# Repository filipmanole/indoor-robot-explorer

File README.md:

<!-- PROJECT SHIELDS -->
<!--
*** I'm using markdown "reference style" links for readability.
*** Reference links are enclosed in brackets [ ] instead of parentheses ( ).
*** See the bottom of this document for the declaration of the reference variables
*** for contributors-url, forks-url, etc. This is an optional, concise syntax you may use.
*** https://www.markdownguide.org/basic-syntax/#reference-style-links
-->

[![Contributors][contributors-shield]][contributors-url]
[![Forks][forks-shield]][forks-url]
[![Stargazers][stars-shield]][stars-url]
[![Issues][issues-shield]][issues-url]
[![LinkedIn][linkedin-shield]][linkedin-url]

<!-- PROJECT LOGO -->
<br />
<p align="center">

  <h1 align="center">Indoor Robot Explorer</h1>

  <p align="center">
    <a href="https://github.com/filipmanole/indoor-robot-explorer/issues">Report Bug</a>
    ·
    <a href="https://github.com/filipmanole/indoor-robot-explorer/issues">Request Feature</a>
  </p>
</p>

<!-- TABLE OF CONTENTS -->

## Table of Contents

- [About the Project](#about-the-project)
- [Software Tools](#software-tools)
- [Hardware](#hardware)
- [Getting Started](#getting-started)
  - [Prerequisites](#prerequisites)
  - [Usage](#usage)
- [Roadmap](#roadmap)
- [Contributing](#contributing)
- [License](#license)

<!-- ABOUT THE PROJECT -->

## About The Project

In recent years there has been an increase in interest in robots. There are billions of dollar spent on professional and personal use robots: autonomous vehicles, maintenance robots, cleaning robots. This repository offers a well structured, modular and low cost robot.

## Software Tools

Board layout was designed using [EAGLE 9.2.2](https://www.autodesk.com/products/eagle/overview?plc=F360&term=1-YEAR&support=ADVANCED&quantity=1)

Firmware was developed using:
- [MPLAB X 5.30](https://www.microchip.com/mplab/mplab-x-ide)
- dsPIC33E-GM-GP-MC-GU-MU_DFP 1.0.23
- [XC16](https://www.microchip.com/mplab/compilers) v1.50

Raspberry Pi specifications:
- [Raspbian GNU/Linux 9 (stretch)](https://www.raspberrypi.org/downloads/raspberry-pi-os/)
- [GCC](https://gcc.gnu.org/) version 6.3.0
- Python 2.7

## Hardware

### Main Components Used
- LiPo Battery 7V4 2200mA
- [dsPIC33EP128GM304](https://www.microchip.com/wwwproducts/en/dsPIC33EP128GM304) microcontroller
- 2x [MC33926](https://www.nxp.com/docs/en/data-sheet/MC33926.pdf) Motor Drivers
- 2x [Pololu ](https://www.pololu.com/product/2283) DC Motors
- 3x [VL53L0X]() Time of Flight Sensors
- [Raspberry Pi Zero W](https://www.raspberrypi.org/products/raspberry-pi-zero-w/)

In the `eagle_project` directory can be found the schematic, the layout design of the board and the Bill of Material. Those files can be used to send the board to manufacture and build the robot. You should obtain something like:

<!-- GETTING STARTED -->

## Getting Started

To get a local copy up and running follow these simple example steps.

### Prerequisites

Make sure you have the following:
- The tools specified in [Software Tools](#software-tools) section
- The robot obtained from the files in the `eagle_project` directory
- [PICkit™ 3](https://www.microchip.com/DevelopmentTools/ProductDetails/PG164130) to programm the robot
- `ssh` connection to the Raspberry Pi Zero W.

```sh
git clone https://github.com/filipmanole/indoor-robot-explorer.git
```

<!-- USAGE EXAMPLES -->

### Usage

Program the robot:
1. Open the MPLAB X project `driver.X`
2. Right click on the project and select `Build`
3. Program the robot using the PICkit 3

Copy the directory `robot-utils` on the Raspberry Pi:
```sh
scp robot-utils/ pi_user@raspberry_pi_address:~
```
Log on the Raspberry Pi:
```sh
ssh pi_user@raspberry_pi_address
```
Run commands to move the robots:
```sh
cd ~/robot-utils/commands
make build
robot start        # robot can be controlled now
robot run 0.3 0.1  # first argument is the linear velocity, the second is the angular velocity
robot pose         # returns the position of the robot x, y and tetha
robot stop         # the robot stops
```

Example of how to get data from the sensors:
```sh
cd ~/robot-utils/tof/VL53L0X
python VL53L0X_multi_example.py
```

<!-- ROADMAP -->

## Roadmap

See the [open issues](https://github.com/filipmanole/indoor-robot-explorer/issues) for a list of proposed features (and known issues).

<!-- CONTRIBUTING -->

## Contributing

Contributions are what make the open source community such an amazing place to be learn, inspire, and create. Any contributions you make are **greatly appreciated**.

1. Fork the Project
2. Create your Feature Branch (`git checkout -b feature/AmazingFeature`)
3. Commit your Changes (`git commit -m 'Add some AmazingFeature'`)
4. Push to the Branch (`git push origin feature/AmazingFeature`)
5. Open a Pull Request

<!-- LICENSE -->

## License

Distributed under the MIT License.

<!-- CONTACT -->

<!-- ACKNOWLEDGEMENTS -->

<!-- MARKDOWN LINKS & IMAGES -->
<!-- https://www.markdownguide.org/basic-syntax/#reference-style-links -->

[contributors-shield]: https://img.shields.io/github/contributors/filipmanole/indoor-robot-explorer.svg?style=flat-square
[contributors-url]: https://github.com/filipmanole/indoor-robot-explorer/graphs/contributors
[forks-shield]: https://img.shields.io/github/forks/filipmanole/indoor-robot-explorer.svg?style=flat-square
[forks-url]: https://github.com/filipmanole/indoor-robot-explorer/network/members
[stars-shield]: https://img.shields.io/github/stars/filipmanole/indoor-robot-explorer.svg?style=flat-square
[stars-url]: https://github.com/filipmanole/indoor-robot-explorer/stargazers
[issues-shield]: https://img.shields.io/github/issues/filipmanole/indoor-robot-explorer.svg?style=flat-square
[issues-url]: https://github.com/filipmanole/indoor-robot-explorer/issues
[linkedin-shield]: https://img.shields.io/badge/-LinkedIn-black.svg?style=flat-square&logo=linkedin&colorB=555
[linkedin-url]: https://www.linkedin.com/in/filip-george-manole/
[product-screenshot]: screenshot.png

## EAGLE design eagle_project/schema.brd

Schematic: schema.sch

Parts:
3V3, 3V3@2, 3V3@3, 3V3@4, 5V: TPB1,27; B1,27
C1, C2, C3: 0.1uF; C0402K; MANUFACTURER_PART_NUMBER CC0402KRX7R7BB104
C4, C46: 10uF; C1210K; MANUFACTURER_PART_NUMBER TAJB106K016TNJ
C5, C20: 33nF; C0603K; MANUFACTURER_PART_NUMBER CC0603KRX7R9BB333
C6, C11, C12, C13, C21, C26, C27, C45, C48, C49, C50, C51: 0.1uF; C0603K; MANUFACTURER_PART_NUMBER CC0603KRX7R9BB104
C7, C22: 0.47uF; C0603K; MANUFACTURER_PART_NUMBER TMK107B7474KA-TR
C8, C9, C10: 1nF; C0402K; MANUFACTURER_PART_NUMBER AC0402KRX7R7BB102
C14, C15: 8pF; C0402K; MANUFACTURER_PART_NUMBER GCM1555C1H8R0DA16D
C16, C23: 1uF; C0603K; MANUFACTURER_PART_NUMBER UMK107AB7105KA-T
C17: 100uF; CAPMP7141X430
C18, C19: 100uF; CAPAE660X770
C24, C25: 10uF; C1206K; MANUFACTURER_PART_NUMBER GMK316AB7106KL-TR
C28, C29: 22uF; C1206; MANUFACTURER_PART_NUMBER EMK316BB7226ML-T
C30: DNP; C1206
C31, C34, C35, C36, C38, C40, C41: DNP; C0603K
C32: 1nF; C0603K; MANUFACTURER_PART_NUMBER 885012206083
C33, C42: 100uF; CAPAE660X800
C37, C39: 100pF; C0603K; MANUFACTURER_PART_NUMBER 885342206001
C43, C44: 10uF; C1210K; MANUFACTURER_PART_NUMBER GRM32DR71E106MA12L
D1: LED0805; LEDC2012X80
ENC1, ENC2: 2283; 1X06/90
FB1: FERRITE_BEADS0805; BEADC2012X105
IC3: RASPBERRY_PI_ZERO_W_(V1.3)NO_HOLE; PI_0_W
J1: XT60
L1: 3.3uH; INDDFN700X690X400-2
LIPO: TPB1,27; B1,27
OA1: AMPLIFIERSOT25; SOT95P285X115-5
P1: POTENSIOMETER; PVG3A
PC: TPB1,27; B1,27
PD: TPB1,27; B1,27
PG: PICkit3; 1X06
PIRX: TPB1,27; B1,27
PITX: TPB1,27; B1,27
R1, R30, R31, R35: 1k; R0603; MANUFACTURER_PART_NUMBER ERJ-3RBD102V
R2, R8, R10, R11, R29: 10k; R0603; MANUFACTURER_PART_NUMBER ERJ-3RBD1002V
R3, R12, R14, R15, R16, R17, R18, R19, R20, R21, R22, R23, R24, R25, R26, R27, R43, R44: 330; R0603; MANUFACTURER_PART_NUMBER RC0603FR-07330RL
R4, R13: 220; R0603; MANUFACTURER_PART_NUMBER UCR03EVPFLR220
R5: DNP; R0402
R6, R7, R28, R41, R42, R45, R46: 100; R0603; MANUFACTURER_PART_NUMBER AC0603FR-13100RL
R9: 54k9; R0603; MANUFACTURER_PART_NUMBER ERJ-PB3B5492V
R32, R36, R47, R61, R62, R63, R64: DNP; R0603
R33, R34, R39, R40: 4k3; R0603; MANUFACTURER_PART_NUMBER AC0603FR-074K3L
R37: 2M; R0805; MANUFACTURER_PART_NUMBER ERJ-6RED2003V
R38: 1M; R0805; MANUFACTURER_PART_NUMBER AC0805FR-13100KL
R53: 240; R0603; MANUFACTURER_PART_NUMBER ERJ-3RBD2400V
R65, R66: 4k7; R0603; MANUFACTURER_PART_NUMBER SFR03EZPF4701
S1: BUTON_SPST; BUTON_SMD
TOF1, TOF2, TOF3: VL53L0X; 1X07/90
U1: DSPIC33EP128GM304TFQP44_WITH3D; QFP80P1200X1200X120-44
U2, U3: NXP_DRIVER; QFN80P800X800X220-33N
U4: TPS656201TPS565201; SOT95P280X110-6
U5: TL1963A-33DCQRDCQ; SOT127P706X180-6
U$1, U$2, U$3, U$4: MOUNTING_HOLE; HOLE_3.5MM
X1: XTALLECX; OSCCC250X200X60

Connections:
3V3: 3V3.TP, 3V3@2.TP, 3V3@3.TP, 3V3@4.TP, C1.2, C2.1, C8.2, C9.1, C44.1, C48.1, C49.1, C50.1, FB1.1, OA1.5 (VDD), P1.1 (3), PG.2, R2.2, R11.2, R29.1, R32.1, R36.1, R62.2, R63.2, R65.2, R66.2, TOF1.7, TOF2.7, TOF3.7, U1.28 (VDD), U1.40 (VDD), U5.4 (OUT), U5.5 (ADJ)
5V: 5V.TP, C12.2, C13.2, C19.1 (POSITIVE), C28.1, C29.1, C30.1, C31.1, C43.2, C45.2, C46.1, ENC1.3, ENC2.4, IC3.2 (+5V_1), IC3.4 (+5V_2), L1.2, R9.2, U5.1 (!SHDN), U5.2 (IN)
!MCLR: PG.1, R28.2, U1.18 (!MCLR)
GND: C1.1, C2.2, C3.1, C4.1, C6.1, C7.2, C8.1, C9.2, C10.1, C11.2, C12.1, C13.1, C14.1, C15.2, C16.2, C17.1 (NEGATIVE), C18.2 (NEGATIVE), C19.2 (NEGATIVE), C21.1, C22.2, C23.2, C24.2, C25.2, C26.2, C28.2, C29.2, C30.2, C32.2, C33.2 (NEGATIVE), C34.2, C36.2, C38.2, C41.2, C42.2 (NEGATIVE), C43.1, C44.2, C45.1, C46.2, C48.2, C49.2, C50.2, C51.2, D1.1 (-), ENC1.4, ENC2.3, IC3.6 (GND_1), IC3.9 (GND_2), IC3.14 (GND_3), IC3.20 (GND_4), IC3.25 (GND_5), IC3.30 (GND_6), IC3.34 (GND_7), IC3.39 (GND_8), J1.2 (-), OA1.2 (GND), P1.3 (1), PG.3, R4.1, R10.1, R13.1, R34.1, R38.2, R40.1, R61.1, R64.1, S1.1, S1.2, TOF1.5, TOF2.5, TOF3.5, U1.6 (VSS), U1.16 (AVSS), U1.29 (VSS), U1.39 (VSS), U2.5 (AGND), U2.17 (N.C.), U2.18 (PGND), U2.19 (PGND), U2.20 (PGND), U2.22 (PGND), U2.23 (PGND), U2.24 (PGND), U2.25 (N.C.), U2.33 (AGND), U3.5 (AGND), U3.17 (N.C.), U3.18 (PGND), U3.19 (PGND), U3.20 (PGND), U3.22 (PGND), U3.23 (PGND), U3.24 (PGND), U3.25 (N.C.), U3.33 (AGND), U4.1 (GND), U5.3 (GND), U5.6 (GND), U$1.P$1, U$2.P$1, U$3.P$1, U$4.P$1, X1.2 (GND), X1.4 (GND)
GPIO1: R7.2, TOF1.4
GPIO2: R46.2, TOF2.4
GPIO3: R42.2, TOF3.4
LIPO: C5.2, C6.2, C16.1, C17.2 (POSITIVE), C18.1 (POSITIVE), C20.2, C21.2, C23.1, C24.1, C25.1, C26.1, C33.1 (POSITIVE), C42.1 (POSITIVE), J1.1 (+), LIPO.TP, R8.2, R37.2, U2.4 (VPWR), U2.6 (VPWR), U2.11 (VPWR), U2.31 (VPWR), U3.4 (VPWR), U3.6 (VPWR), U3.11 (VPWR), U3.31 (VPWR), U4.3 (VIN)
LIPO_ADC: OA1.1 (OUT), OA1.4 (IN-), R47.1, U1.22 (RB1)
M1_!D2: R18.1, U1.12 (RA10)
M1_!SF: R3.1, U1.38 (RC5)
M1_D1: R20.2, U1.13 (RA7)
M1_EN: R25.1, U1.37 (RC4)
M1_FB: C7.1, C40.1, C41.1, R1.1, R35.1
M1_IN1: R17.2, U1.14 (RB14)
M1_IN2: R16.2, U1.15 (RB15)
M1_INV: R14.1, U1.36 (RC3)
M1_OUT1: ENC1.6, U2.12 (OUT1), U2.13 (OUT1), U2.14 (OUT1), U2.15 (OUT1)
M1_OUT2: ENC1.5, U2.27 (OUT2), U2.28 (OUT2), U2.29 (OUT2), U2.30 (OUT2)
M1_QEA: ENC1.2, U1.10 (RB12)
M1_QEB: ENC1.1, U1.11 (RB13)
M1_SLEW: R15.2, U1.35 (RA9)
M2_!D2: R26.1, U1.2 (RC6)
M2_!SF: R12.1, U1.41 (RB5)
M2_D1: R27.2, U1.3 (RC7)
M2_EN: R19.1, U1.44 (RB8)
M2_FB: C22.1, C34.1, C35.1, R30.1, R31.1
M2_IN1: R22.1, U1.4 (RC8)
M2_IN2: R21.1, U1.5 (RC9)
M2_INV: R24.1, U1.42 (RB6)
M2_OUT1: ENC2.2, U3.12 (OUT1), U3.13 (OUT1), U3.14 (OUT1), U3.15 (OUT1)
M2_OUT2: ENC2.1, U3.27 (OUT2), U3.28 (OUT2), U3.29 (OUT2), U3.30 (OUT2)
M2_QEA: ENC2.5, U1.8 (RB10)
M2_QEB: ENC2.6, U1.9 (RB11)
M2_SLEW: R23.1, U1.43 (RB7)
unnamed: R53.2, U1.1 (RB9)
unnamed: IC3.33 (GPIO13/PWM1), R41.1
unnamed: C27.2, U4.6 (VBST)
unnamed: C31.2, R9.1, R10.2, U4.4 (VFB)
unnamed: R14.2, U2.7 (INV)
unnamed: R21.2, U3.1 (IN2)
unnamed: R8.1, U4.5 (EN)
unnamed: R22.2, U3.2 (IN1)
unnamed: C4.2, U1.7 (VCAP)
unnamed: C27.1, L1.1, U4.2 (SW)
unnamed: R23.2, U3.3 (SLEW)
unnamed: R24.2, U3.7 (INV)
unnamed: R26.2, U3.16 (!D2)
unnamed: R27.1, U3.26 (D1)
unnamed: R20.1, U2.26 (D1)
unnamed: R16.1, U2.1 (IN2)
unnamed: R17.1, U2.2 (IN1)
unnamed: R15.1, U2.3 (SLEW)
unnamed: R18.2, U2.16 (!D2)
unnamed: R11.1, R12.2, U3.21 (!SF)
unnamed: IC3.35 (GPIO19/SPI0_MISO1/PWM1), R7.1
unnamed: R2.1, R3.2, U2.21 (!SF)
unnamed: R25.2, R64.2, U2.9 (N.C.), U2.10 (EN)
unnamed: R4.2, R30.2, U3.8 (FB)
unnamed: C5.1, U2.32 (CCP)
unnamed: R19.2, R61.2, U3.9 (N.C.), U3.10 (EN)
unnamed: IC3.36 (GPIO16/SPI1_CS2), R42.1
unnamed: IC3.37 (GPIO26), R6.1
unnamed: IC3.38 (GPIO20/SPI0_MOSI1), R45.1
unnamed: IC3.40 (GPIO21/SPI0_SCLK1), R46.1
unnamed: R1.2, R13.2, U2.8 (FB)
unnamed: C11.1, OA1.3 (IN+), R37.1, R38.1, R47.2
unnamed: IC3.8 (GPIO_14/[UART]_TXD0), PITX.TP, R43.2
unnamed: IC3.10 (GPIO_15/[UART]_RXD0), PIRX.TP, R44.2
unnamed: D1.2 (+), R53.1
unnamed: C3.2, C10.2, FB1.2, U1.17 (AVDD)
unnamed: C20.1, U3.32 (CCP)
OA2IN+: C35.2, R31.2, R63.1, U1.20 (RA1)
OA2IN-: C36.1, C37.2, R32.2, R33.1, R34.2, U1.21 (RB0)
OA2OUT: C37.1, R33.2, U1.19 (RA0)
OA3IN+: C40.2, R35.2, R62.1, U1.27 (RC2)
OA3IN-: C38.1, C39.2, R36.2, R39.1, R40.2, U1.26 (RC1)
OA3OUT: C39.1, R39.2, U1.25 (RC0)
OSC1: C14.2, R5.1, U1.30 (RA2), X1.3 (XTAL)
OSC2: C15.1, R5.2, U1.31 (RA3), X1.1 (XTAL)
PGEC: PC.TP, PG.5, U1.23 (RB2)
PGED: PD.TP, PG.4, U1.24 (RB3)
PI_RX: R44.1, U1.33 (RB4)
PI_TX: R43.1, U1.32 (RA8)
POT_ADC: C51.1, P1.2, U1.34 (RA4)
RESET: C32.1, R28.1, R29.2, S1.3, S1.4
SCL: IC3.5 (GPIO_3/[I2C]_SCL), R65.1, TOF1.2, TOF2.2, TOF3.2
SDA: IC3.3 (GPIO_2/[I2C]_SDA), R66.1, TOF1.1, TOF2.1, TOF3.1
XSHUT1: R6.2, TOF1.3
XSHUT2: R45.2, TOF2.3
XSHUT3: R41.2, TOF3.3

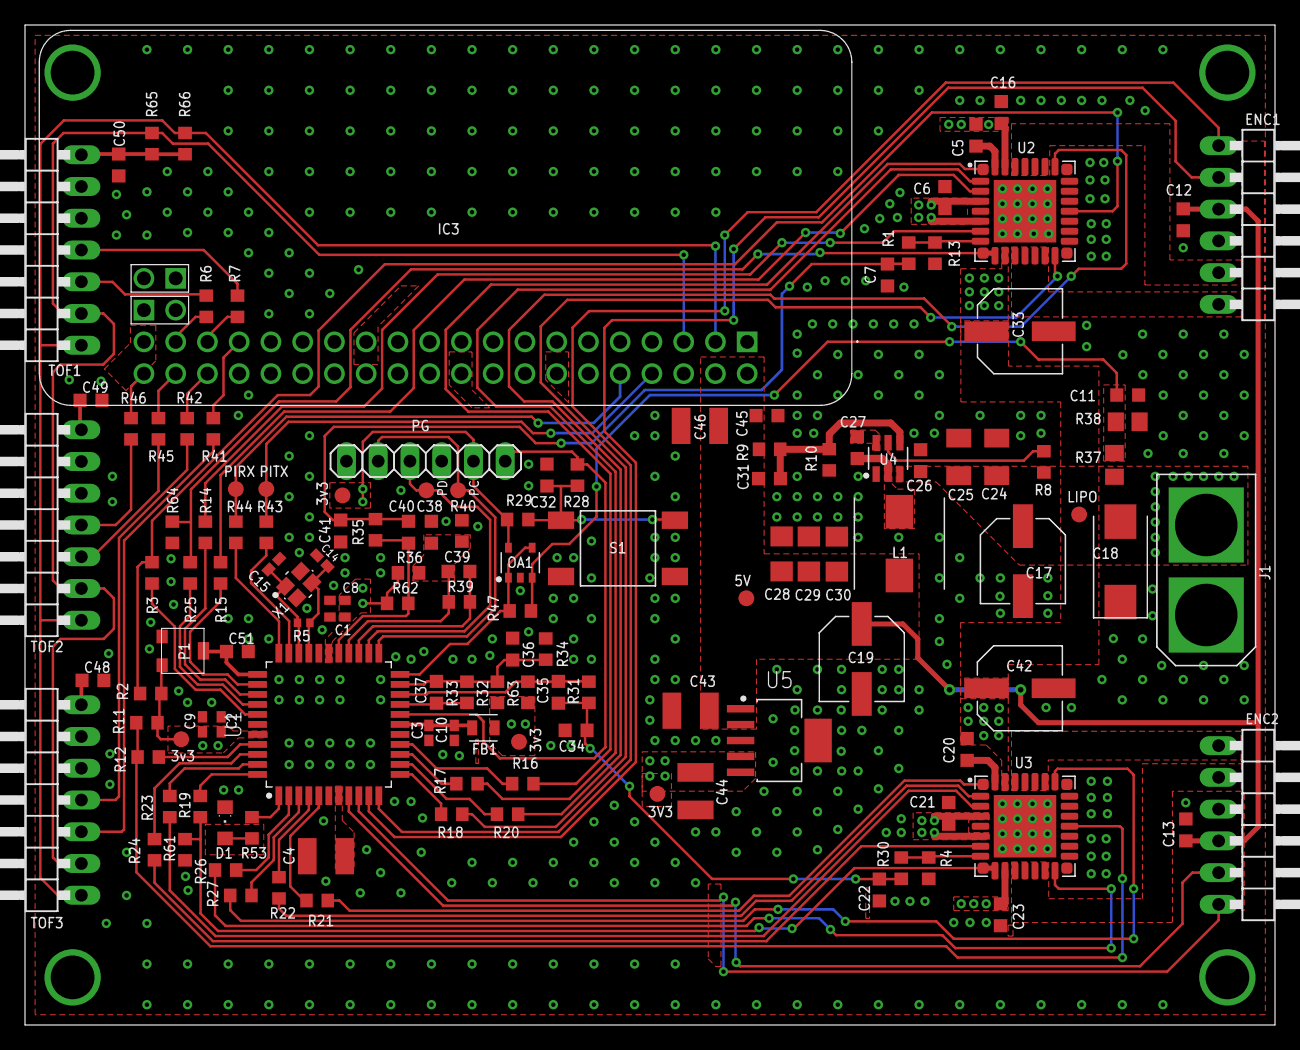
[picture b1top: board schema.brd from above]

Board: 2 copper layers, 100.0 x 80.0 mm, 138 parts (0 on the bottom side), 91 nets.

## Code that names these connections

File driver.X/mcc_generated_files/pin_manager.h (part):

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*/
/**
  @Summary
    Sets the GPIO pin, RA3, high using LATA3.

  @Description
    Sets the GPIO pin, RA3, high using LATA3.

  @Preconditions
    The RA3 must be set to an output.
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#define test_SetHigh()          _LATA3 = 1
/**
  @Summary
    Sets the GPIO pin, RA3, low using LATA3.

  @Description
    Sets the GPIO pin, RA3, low using LATA3.

  @Preconditions
    The RA3 must be set to an output.
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#define test_SetLow()           _LATA3 = 0
/**
  @Summary
    Toggles the GPIO pin, RA3, using LATA3.

  @Description
    Toggles the GPIO pin, RA3, using LATA3.

  @Preconditions
    The RA3 must be set to an output.
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#define test_Toggle()           _LATA3 ^= 1
/**
  @Summary
    Reads the value of the GPIO pin, RA3.

  @Description
    Reads the value of the GPIO pin, RA3.

  @Preconditions
    None.
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    </code>

*/
#define test_GetValue()         _RA3
/**
  @Summary
    Configures the GPIO pin, RA3, as an input.

  @Description
    Configures the GPIO pin, RA3, as an input.

  @Preconditions
    None.
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#define test_SetDigitalInput()  _TRISA3 = 1
/**
  @Summary
    Configures the GPIO pin, RA3, as an output.

  @Description
    Configures the GPIO pin, RA3, as an output.

  @Preconditions
    None.
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#define test_SetDigitalOutput() _TRISA3 = 0
/**
  @Summary
    Sets the GPIO pin, RA7, high using LATA7.

  @Description
    Sets the GPIO pin, RA7, high using LATA7.

  @Preconditions
    The RA7 must be set to an output.
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#define M1_D1_SetHigh()          _LATA7 = 1
/**
  @Summary
    Sets the GPIO pin, RA7, low using LATA7.

  @Description
    Sets the GPIO pin, RA7, low using LATA7.

  @Preconditions
    The RA7 must be set to an output.
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#define M1_D1_SetLow()           _LATA7 = 0
/**
  @Summary
    Toggles the GPIO pin, RA7, using LATA7.

  @Description
    Toggles the GPIO pin, RA7, using LATA7.

  @Preconditions
    The RA7 must be set to an output.
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#define M1_D1_Toggle()           _LATA7 ^= 1
/**
  @Summary
    Reads the value of the GPIO pin, RA7.

  @Description
    Reads the value of the GPIO pin, RA7.

  @Preconditions
    None.
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    </code>

*/
#define M1_D1_GetValue()         _RA7
/**
  @Summary
    Configures the GPIO pin, RA7, as an input.

  @Description
    Configures the GPIO pin, RA7, as an input.

  @Preconditions
    None.
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#define M1_D1_SetDigitalInput()  _TRISA7 = 1
/**
  @Summary
    Configures the GPIO pin, RA7, as an output.

  @Description
    Configures the GPIO pin, RA7, as an output.

  @Preconditions
    None.
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#define M1_D1_SetDigitalOutput() _TRISA7 = 0
/**
  @Summary
    Sets the GPIO pin, RA9, high using LATA9.

  @Description
    Sets the GPIO pin, RA9, high using LATA9.

  @Preconditions
    The RA9 must be set to an output.
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#define M1_SLEW_SetHigh()          _LATA9 = 1
/**
  @Summary
    Sets the GPIO pin, RA9, low using LATA9.

  @Description
    Sets the GPIO pin, RA9, low using LATA9.

  @Preconditions
    The RA9 must be set to an output.
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#define M1_SLEW_SetLow()           _LATA9 = 0
/**
  @Summary
    Toggles the GPIO pin, RA9, using LATA9.

  @Description
    Toggles the GPIO pin, RA9, using LATA9.

  @Preconditions
    The RA9 must be set to an output.
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#define M1_SLEW_Toggle()           _LATA9 ^= 1
/**
  @Summary
    Reads the value of the GPIO pin, RA9.

  @Description
    Reads the value of the GPIO pin, RA9.

  @Preconditions
    None.
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    </code>

*/
#define M1_SLEW_GetValue()         _RA9
/**
  @Summary
    Configures the GPIO pin, RA9, as an input.

  @Description
    Configures the GPIO pin, RA9, as an input.

  @Preconditions
    None.
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#define M1_SLEW_SetDigitalInput()  _TRISA9 = 1
/**
  @Summary
    Configures the GPIO pin, RA9, as an output.

  @Description
    Configures the GPIO pin, RA9, as an output.

  @Preconditions
    None.
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#define M1_SLEW_SetDigitalOutput() _TRISA9 = 0
/**
  @Summary
    Sets the GPIO pin, RB10, high using LATB10.

  @Description
    Sets the GPIO pin, RB10, high using LATB10.

  @Preconditions
    The RB10 must be set to an output.
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#define M2_QEA_SetHigh()          _LATB10 = 1
/**
  @Summary
    Sets the GPIO pin, RB10, low using LATB10.

  @Description
    Sets the GPIO pin, RB10, low using LATB10.

  @Preconditions
    The RB10 must be set to an output.
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#define M2_QEA_SetLow()           _LATB10 = 0
/**
  @Summary
    Toggles the GPIO pin, RB10, using LATB10.

  @Description
    Toggles the GPIO pin, RB10, using LATB10.

  @Preconditions
    The RB10 must be set to an output.
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#define M2_QEA_Toggle()           _LATB10 ^= 1
/**
  @Summary
    Reads the value of the GPIO pin, RB10.

  @Description
    Reads the value of the GPIO pin, RB10.

  @Preconditions
    None.
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    </code>

*/
#define M2_QEA_GetValue()         _RB10
/**
  @Summary
    Configures the GPIO pin, RB10, as an input.

  @Description
    Configures the GPIO pin, RB10, as an input.

  @Preconditions
    None.
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#define M2_QEA_SetDigitalInput()  _TRISB10 = 1
/**
  @Summary
    Configures the GPIO pin, RB10, as an output.

  @Description
    Configures the GPIO pin, RB10, as an output.

  @Preconditions
    None.
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#define M2_QEA_SetDigitalOutput() _TRISB10 = 0
/**
  @Summary
    Sets the GPIO pin, RB11, high using LATB11.

  @Description
    Sets the GPIO pin, RB11, high using LATB11.

  @Preconditions
    The RB11 must be set to an output.
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#define M2_QEB_SetHigh()          _LATB11 = 1
/**
  @Summary
    Sets the GPIO pin, RB11, low using LATB11.

  @Description
    Sets the GPIO pin, RB11, low using LATB11.

  @Preconditions
    The RB11 must be set to an output.
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#define M2_QEB_SetLow()           _LATB11 = 0
/**
  @Summary
    Toggles the GPIO pin, RB11, using LATB11.

  @Description
    Toggles the GPIO pin, RB11, using LATB11.

  @Preconditions
    The RB11 must be set to an output.
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#define M2_QEB_Toggle()           _LATB11 ^= 1
/**
  @Summary
    Reads the value of the GPIO pin, RB11.

  @Description
    Reads the value of the GPIO pin, RB11.

  @Preconditions
    None.
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    </code>

*/
#define M2_QEB_GetValue()         _RB11
/**
  @Summary
    Configures the GPIO pin, RB11, as an input.

  @Description
    Configures the GPIO pin, RB11, as an input.

  @Preconditions
    None.
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#define M2_QEB_SetDigitalInput()  _TRISB11 = 1
/**
  @Summary
    Configures the GPIO pin, RB11, as an output.

  @Description
    Configures the GPIO pin, RB11, as an output.

  @Preconditions
    None.
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#define M2_QEB_SetDigitalOutput() _TRISB11 = 0
/**
  @Summary
    Sets the GPIO pin, RB12, high using LATB12.

  @Description
    Sets the GPIO pin, RB12, high using LATB12.

  @Preconditions
    The RB12 must be set to an output.
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#define M1_QEA_SetHigh()          _LATB12 = 1
/**
  @Summary
    Sets the GPIO pin, RB12, low using LATB12.

  @Description
    Sets the GPIO pin, RB12, low using LATB12.

  @Preconditions
    The RB12 must be set to an output.
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#define M1_QEA_SetLow()           _LATB12 = 0
/**
  @Summary
    Toggles the GPIO pin, RB12, using LATB12.

  @Description
    Toggles the GPIO pin, RB12, using LATB12.

  @Preconditions
    The RB12 must be set to an output.
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#define M1_QEA_Toggle()           _LATB12 ^= 1
/**
  @Summary
    Reads the value of the GPIO pin, RB12.

  @Description
    Reads the value of the GPIO pin, RB12.

  @Preconditions
    None.
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    </code>

*/
#define M1_QEA_GetValue()         _RB12
/**
  @Summary
    Configures the GPIO pin, RB12, as an input.

  @Description
    Configures the GPIO pin, RB12, as an input.

  @Preconditions
    None.
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#define M1_QEA_SetDigitalInput()  _TRISB12 = 1
/**
  @Summary
    Configures the GPIO pin, RB12, as an output.

  @Description
    Configures the GPIO pin, RB12, as an output.

  @Preconditions
    None.
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#define M1_QEA_SetDigitalOutput() _TRISB12 = 0
/**
  @Summary
    Sets the GPIO pin, RB13, high using LATB13.

  @Description
    Sets the GPIO pin, RB13, high using LATB13.

  @Preconditions
    The RB13 must be set to an output.
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#define M1_QEB_SetHigh()          _LATB13 = 1
/**
  @Summary
    Sets the GPIO pin, RB13, low using LATB13.

  @Description
    Sets the GPIO pin, RB13, low using LATB13.

  @Preconditions
    The RB13 must be set to an output.
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#define M1_QEB_SetLow()           _LATB13 = 0
/**
  @Summary
    Toggles the GPIO pin, RB13, using LATB13.

  @Description
    Toggles the GPIO pin, RB13, using LATB13.

  @Preconditions
    The RB13 must be set to an output.
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#define M1_QEB_Toggle()           _LATB13 ^= 1
/**
  @Summary
    Reads the value of the GPIO pin, RB13.

  @Description
    Reads the value of the GPIO pin, RB13.

  @Preconditions
    None.
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    </code>

*/
#define M1_QEB_GetValue()         _RB13
/**
  @Summary
    Configures the GPIO pin, RB13, as an input.

  @Description
    Configures the GPIO pin, RB13, as an input.

  @Preconditions
    None.
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#define M1_QEB_SetDigitalInput()  _TRISB13 = 1
/**
  @Summary
    Configures the GPIO pin, RB13, as an output.

  @Description
    Configures the GPIO pin, RB13, as an output.

  @Preconditions
    None.
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#define M1_QEB_SetDigitalOutput() _TRISB13 = 0
/**
  @Summary
    Sets the GPIO pin, RB14, high using LATB14.
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
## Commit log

2020-06-30 added schematic and layout;added driver implementation
2020-06-30 updated readme; added BOM; added robot-utils
2020-06-30 removed files from .gitignore; readme fix
2020-07-01 Add MIT LICENSE

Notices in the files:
driver.X/mcc_generated_files/pin_manager.h:
(c) 2016 Microchip Technology Inc. and its subsidiaries. You may use this
